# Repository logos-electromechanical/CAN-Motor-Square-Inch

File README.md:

# CAN-Motor-Square-Inch
An entry for the Hackaday One Square Inch contest -- a CANbus 28V/12A brush motor controller with encoder and current feedback.

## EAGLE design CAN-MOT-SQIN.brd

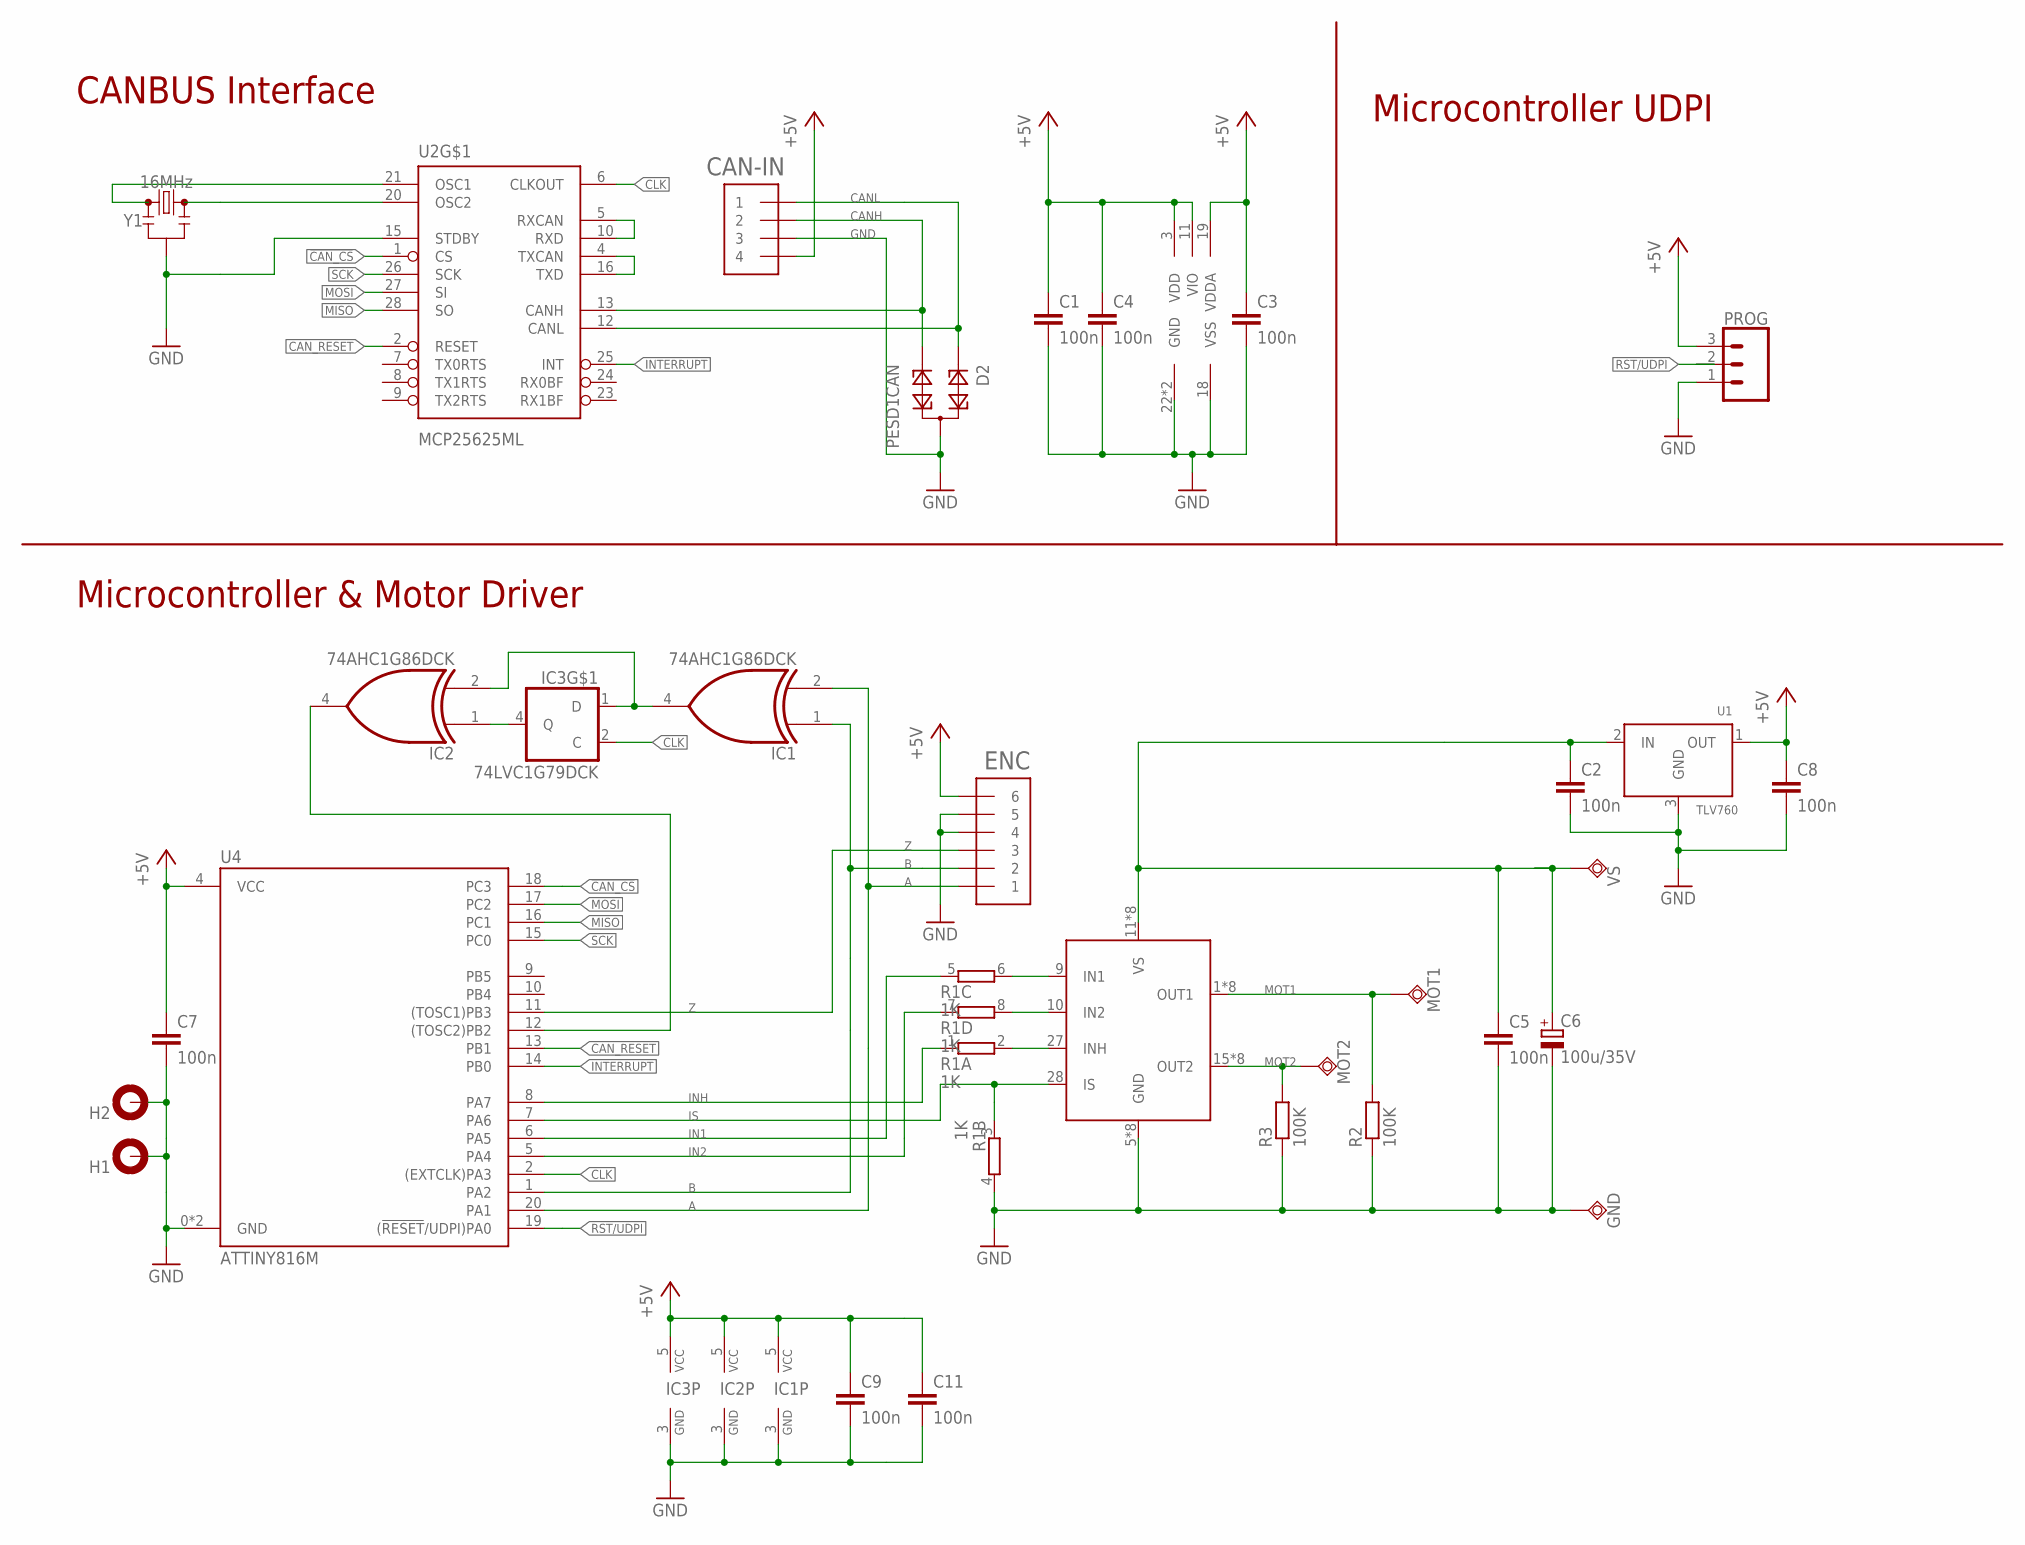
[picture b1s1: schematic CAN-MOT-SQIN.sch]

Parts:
C1, C2, C3, C4, C5, C7, C8, C9, C11: 100n; C0603
C6: 100u/35V; PANASONIC_D
CAN-IN: STRAWSON_EAGLE_LIB_JST_SH_4; STRAWSON_EAGLE_LIB_JST_SH_4_SMD
D2: PESD1CAN; SOT23
ENC: STRAWSON_EAGLE_LIB_JST_SH_6
GND: TPSQTP20SQ; TP20SQ
H1, H2: MOUNT-PAD-ROUND2.8; 2,8-PAD
IC1, IC2: 74AHC1G86DCK; SC70-5
IC3: 74LVC1G79DCK; SC70-5
MOT1, MOT2: TPSQTP20SQ; TP20SQ
PROG: CONN_03LOCK; 1X03_LOCK
R1: 1K; CTS742C083-RES
R2, R3: 100K; R0603
U1: TLV760; SOT23
U2: MCP25625ML; QFN-28(6X6)
U3: BTM7752G; PG-DSO-36-29
U4: ATTINY816M; QFN20
VS: TPSQTP20SQ; TP20SQ
Y1: 16MHz; RESONATOR-SMD-3.2X1.3; PARTNO PRQC16.00CR5010X000

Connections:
!CAN_CS!: U2.1 (CS), U4.18 (PC3)
+5V: C1.1, C3.1, C4.1, C7.1, C8.1, C9.1, C11.1, CAN-IN.4, ENC.6, IC1.5 (VCC), IC2.5 (VCC), IC3.5 (VCC), PROG.3, U1.1 (OUT), U2.3 (VDD), U2.11 (VIO), U2.19 (VDDA), U4.4 (VCC)
A: ENC.1, IC1.2 (I1), U4.20 (PA1)
B: ENC.2, IC1.1 (I0), U4.1 (PA2)
CANH: CAN-IN.2, D2.2, U2.13 (CANH)
CANL: CAN-IN.1, D2.1, U2.12 (CANL)
CAN_RESET: U2.2 (RESET), U4.13 (PB1)
CLK: IC3.2 (C), U2.6 (CLKOUT), U4.2 ((EXTCLK)PA3)
GND: C1.2, C2.2, C3.2, C4.2, C5.2, C6.-, C7.2, C8.2, C9.2, C11.2, CAN-IN.3, D2.3, ENC.4, ENC.5, GND.TP, H1.B2,8, H2.B2,8, IC1.3 (GND), IC2.3 (GND), IC3.3 (GND), PROG.1, R1.4 (2), R2.1, R3.1, U1.3 (GND), U2.15 (STDBY), U2.18 (VSS), U2.22 (GND), U2.EP (GND), U3.5 (GND), U3.6 (GND), U3.7 (GND), U3.8 (GND), U3.23 (GND), U3.24 (GND), U3.25 (GND), U3.26 (GND), U4.0 (GND), U4.3 (GND), Y1.2
IN1: R1.5 (1), U4.6 (PA5)
IN2: R1.7 (1), U4.5 (PA4)
INH: R1.1, U4.8 (PA7)
INTERRUPT: U2.25 (INT), U4.14 (PB0)
IS: R1.3 (1), U3.28 (IS), U4.7 (PA6)
MISO: U2.28 (SO), U4.16 (PC1)
MOSI: U2.27 (SI), U4.17 (PC2)
MOT1: MOT1.TP, R2.2, U3.1 (OUT1), U3.2 (OUT1), U3.3 (OUT1), U3.4 (OUT1), U3.33 (OUT1), U3.34 (OUT1), U3.35 (OUT1), U3.36 (OUT1)
MOT2: MOT2.TP, R3.2, U3.15 (OUT2), U3.16 (OUT2), U3.17 (OUT2), U3.18 (OUT2), U3.19 (OUT2), U3.20 (OUT2), U3.21 (OUT2), U3.22 (OUT2)
unnamed: U2.4 (TXCAN), U2.16 (TXD)
unnamed: U2.5 (RXCAN), U2.10 (RXD)
unnamed: R1.6 (2), U3.9 (IN1)
unnamed: IC2.1 (I0), IC3.4 (Q)
unnamed: IC1.4 (O), IC2.2 (I1), IC3.1 (D)
unnamed: R1.8 (2), U3.10 (IN2)
unnamed: R1.2, U3.27 (INH)
unnamed: IC2.4 (O), U4.12 ((TOSC2)PB2)
unnamed: U2.21 (OSC1), Y1.1
unnamed: U2.20 (OSC2), Y1.3
RST/UDPI: PROG.2, U4.19 ((!RESET!/UDPI)PA0)
SCK: U2.26 (SCK), U4.15 (PC0)
VS: C2.1, C5.1, C6.+, U1.2 (IN), U3.11 (VS), U3.12 (VS), U3.13 (VS), U3.14 (VS), U3.29 (VS), U3.30 (VS), U3.31 (VS), U3.32 (VS), VS.TP
Z: ENC.3, U4.11 ((TOSC1)PB3)

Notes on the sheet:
CANBUS Interface
Microcontroller & Motor Driver
Microcontroller UDPI

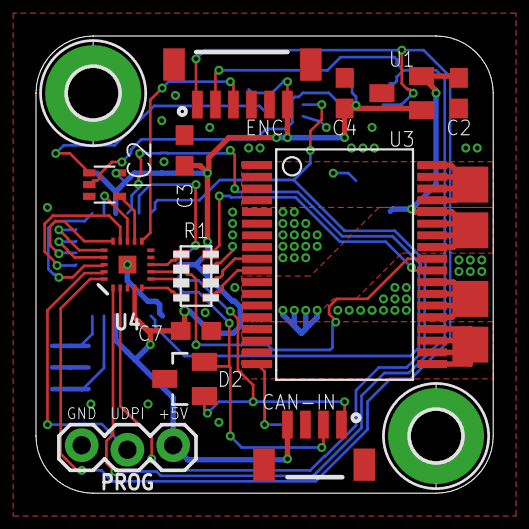
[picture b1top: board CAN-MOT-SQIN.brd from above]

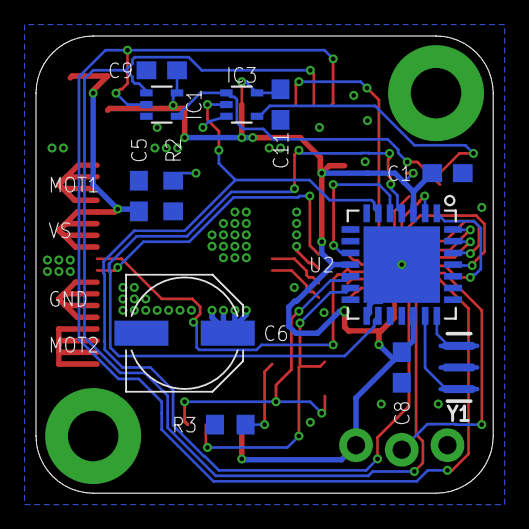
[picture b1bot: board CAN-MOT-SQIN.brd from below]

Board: 2 copper layers, 25.4 x 25.4 mm, 31 parts (12 on the bottom side), 32 nets.

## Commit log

2018-08-11 Now with better silkscreen
2018-08-15 Re-routed so now the peripherals will do the right thing
2018-08-22 Fixed the routing so now it will (probably) work as intended
2018-09-02 Revised with the correct ATTINY816 footprint and external logic for the encoder
2018-10-01 Added gerber files

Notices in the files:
parts and their libraries:
SparkFun-Clocks: Licensing: Creative Commons ShareAlike 4.0 International - https://creativecommons.org/licenses/by-sa/4.0
